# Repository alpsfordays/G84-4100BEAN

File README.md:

# G84-4100BEAN
A ZMK drop-in replacement PCB for the G84-4100 based on the nice!nano and its clones.

## Licence
This project is licenced under the No Wastemans licence. Effectively CC BY-SA 4.0 with exceptions for wastemans, who are afforded no reuse, distribution or manufacture rights whatsoever. For everyone else, it would be great (but not required) if you let me know what you do with it!

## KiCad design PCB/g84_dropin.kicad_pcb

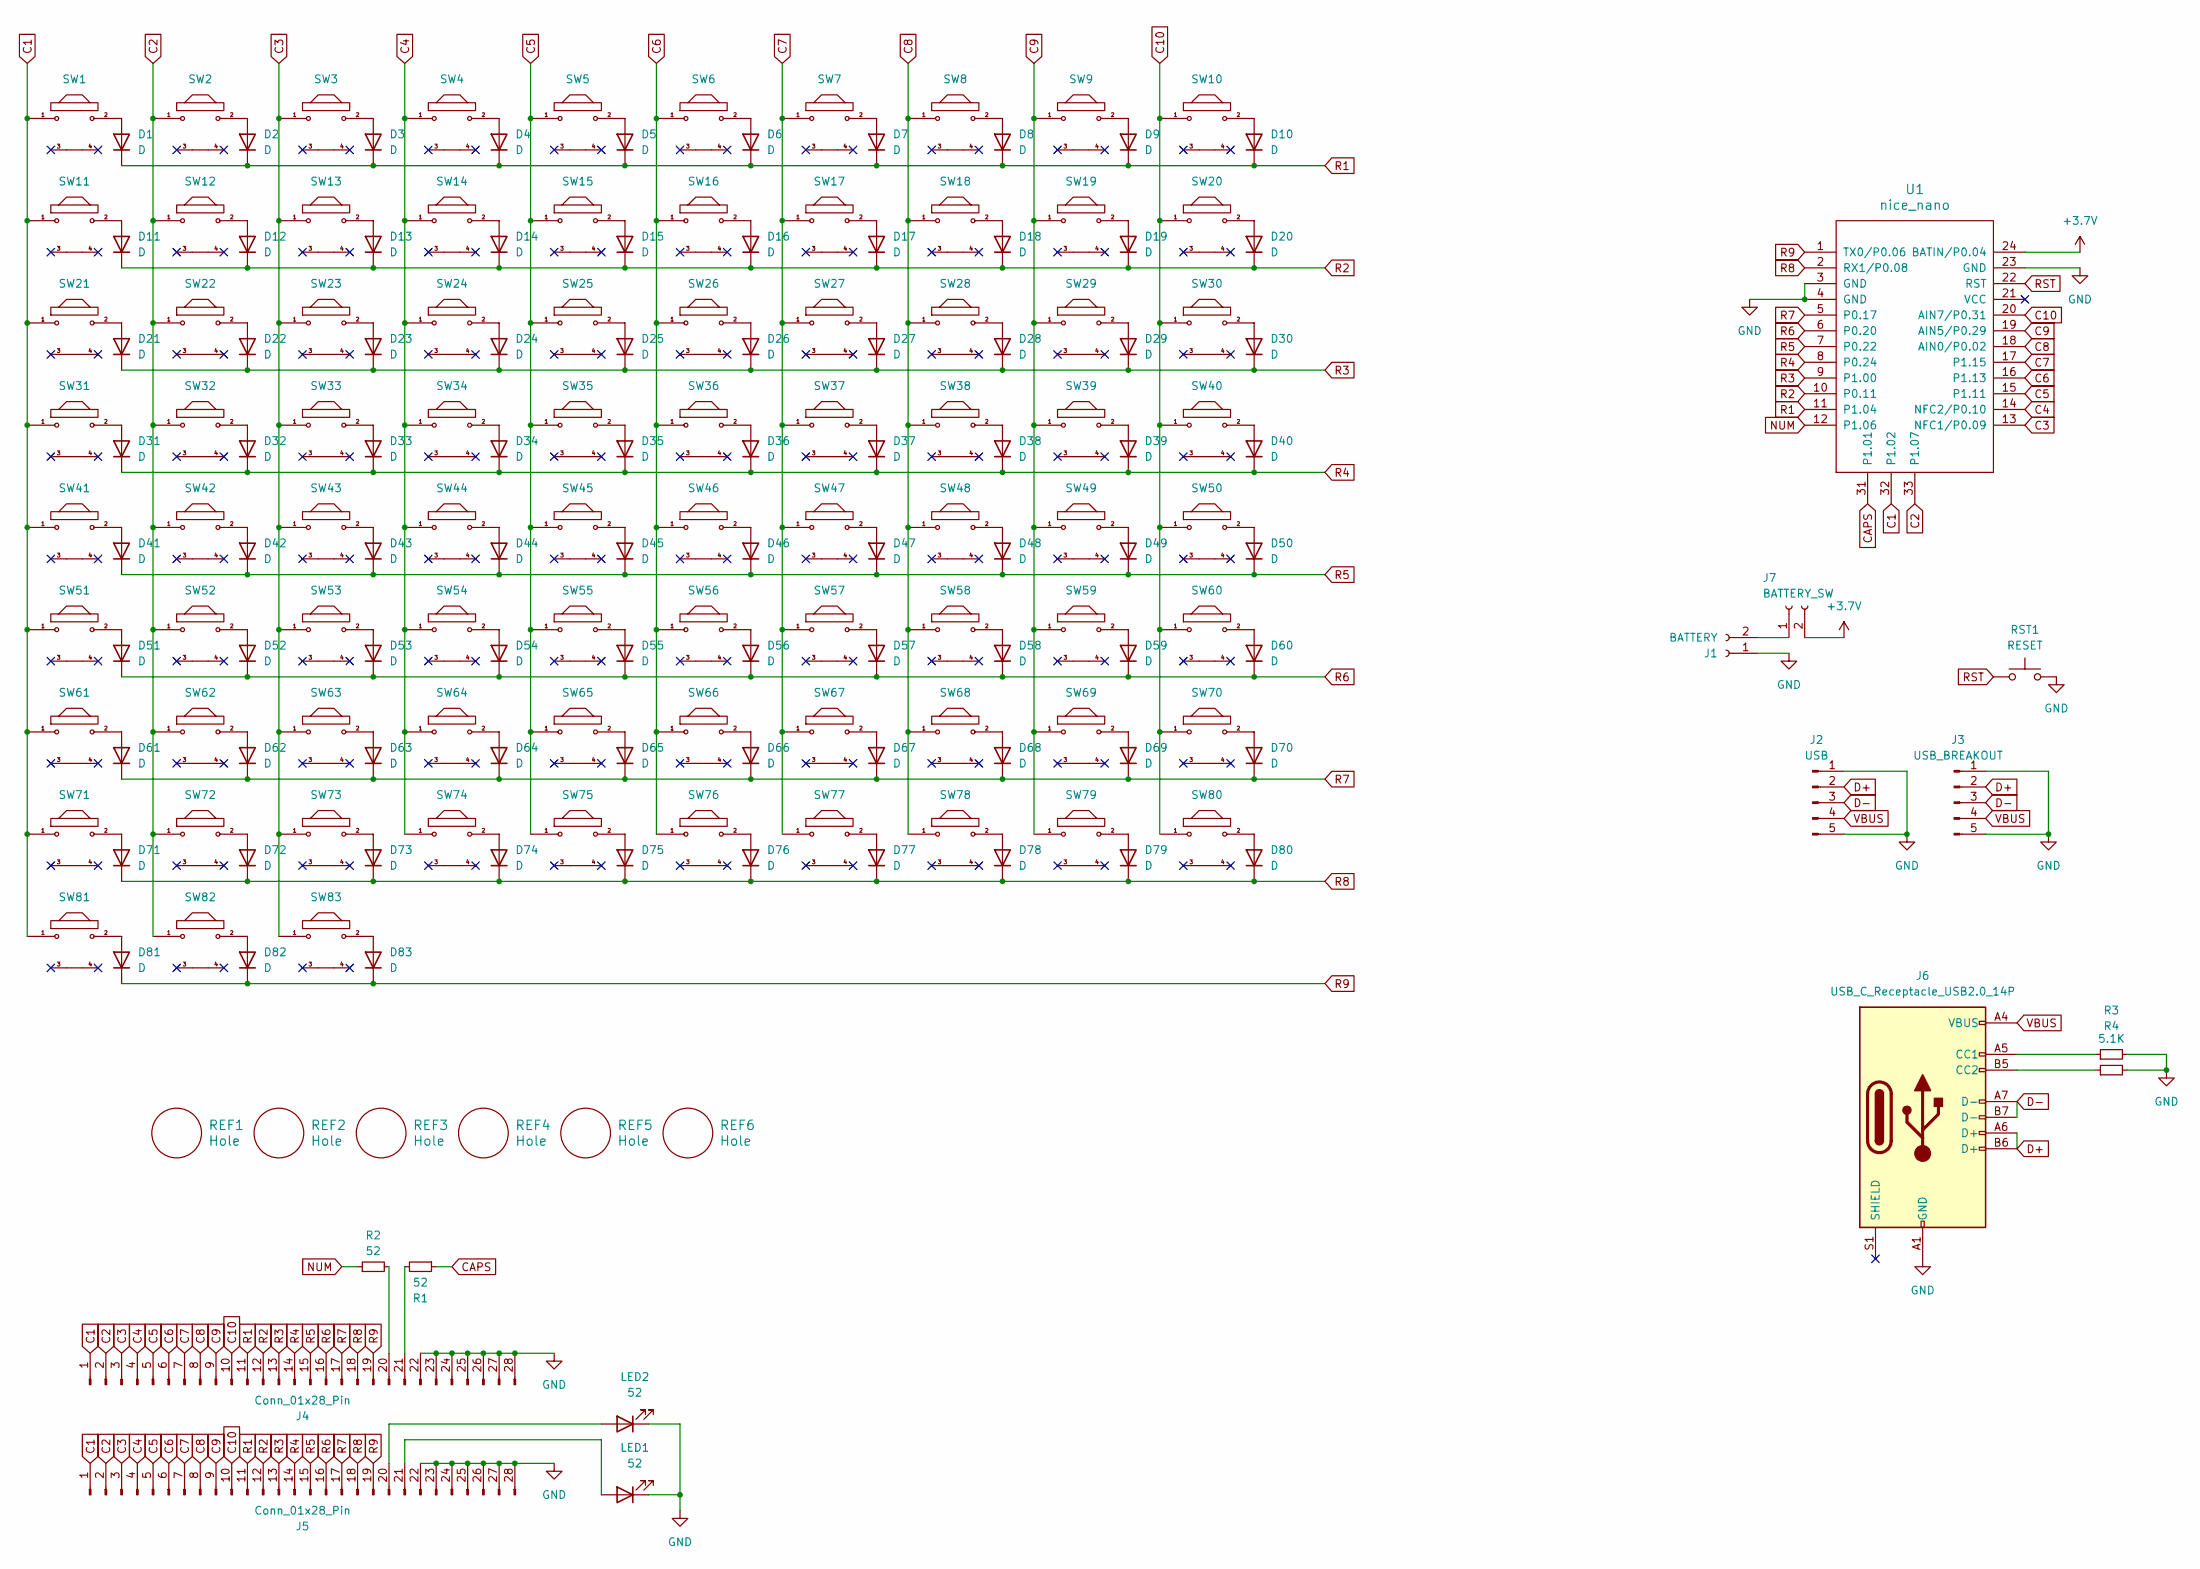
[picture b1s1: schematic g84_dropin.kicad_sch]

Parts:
D1, D2, D3, D4, D5, D6, D7, D8, D9, D10, D11, D12, D13, D14, D15, D16, D17, D18, D19, D20, D21, D22, D23, D24, D25, D26, D27, D28, D29, D30, D31, D32, D33, D34, D35, D36, D37, D38, D39, D40, D41, D42, D43, D44, D45, D46, D47, D48, D49, D50, D51, D52, D53, D54, D55, D56, D57, D58, D59, D60, D61, D62, D63, D64, D65, D66, D67, D68, D69, D70, D71, D72, D73, D74, D75, D76, D77, D78, D79, D80, D81, D82, D83: D; D_0805
J1: BATTERY; PinSocket_1x02_P2.54mm_Vertical
J2: USB; PinHeader_1x05_P1.27mm_Vertical
J3: USB_BREAKOUT; PinHeader_1x05_P2.54mm_Vertical
J4, J5: Conn_01x28_Pin; PinSocket_1x28_P1.27mm_Vertical
J6: USB_C_Receptacle_USB2.0_14P; TYPE-C-31-M-12
J7: BATTERY_SW; PinSocket_1x02_P2.54mm_Vertical
LED1, LED2: 52; D_0805
R1, R2: 52; R_0805
R3, R4: 5.1K; R_0805
REF1, REF2, REF3, REF4, REF5, REF6: Hole; breakaway-mousebites
RST1: RESET; SW_Push_1P1T_XKB_TS-1187A
SW1, SW2, SW3, SW4, SW5, SW6, SW7, SW8, SW9, SW10, SW12, SW13, SW14, SW15, SW16, SW17, SW18, SW19, SW20, SW21, SW22, SW23, SW24, SW25, SW26, SW27, SW28, SW29, SW30, SW32, SW33, SW34, SW35, SW36, SW37, SW38, SW39, SW40, SW42, SW43, SW44, SW45, SW46, SW47, SW48, SW49, SW50, SW51, SW52, SW53, SW54, SW56, SW57, SW58, SW61, SW62, SW68, SW69, SW70, SW71, SW77, SW78: ML; THIN_ML_1u
SW11: ML; THIN_ML_1uL
SW31, SW67, SW80: ML; THIN_ML_1.25u
SW41: ML; THIN_ML_1.75u
SW55: ML; THIN_ML_5u
SW59, SW60, SW63, SW64, SW65, SW66, SW72, SW73, SW74, SW75, SW79, SW81, SW82, SW83: ML; THIN_ML_1uS
SW76: ML; THIN_ML_1.5u
U1: nice_nano; nice_nano_clone_combo

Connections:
+3.7V: J7.2, U1.24 (BATIN/P0.04)
C1: J4.1, J5.1, SW1.1, SW11.1, SW21.1, SW31.1, SW41.1, SW51.1, SW61.1, SW71.1, SW81.1, U1.32 (P1.02)
C2: J4.2, J5.2, SW2.1, SW12.1, SW22.1, SW32.1, SW42.1, SW52.1, SW62.1, SW72.1, SW82.1, U1.33 (P1.07)
C3: J4.3, J5.3, SW3.1, SW13.1, SW23.1, SW33.1, SW43.1, SW53.1, SW63.1, SW73.1, SW83.1, U1.13 (NFC1/P0.09)
C4: J4.4, J5.4, SW4.1, SW14.1, SW24.1, SW34.1, SW44.1, SW54.1, SW64.1, SW74.1, U1.14 (NFC2/P0.10)
C5: J4.5, J5.5, SW5.1, SW15.1, SW25.1, SW35.1, SW45.1, SW55.1, SW65.1, SW75.1, U1.15 (P1.11)
C6: J4.6, J5.6, SW6.1, SW16.1, SW26.1, SW36.1, SW46.1, SW56.1, SW66.1, SW76.1, U1.16 (P1.13)
C7: J4.7, J5.7, SW7.1, SW17.1, SW27.1, SW37.1, SW47.1, SW57.1, SW67.1, SW77.1, U1.17 (P1.15)
C8: J4.8, J5.8, SW8.1, SW18.1, SW28.1, SW38.1, SW48.1, SW58.1, SW68.1, SW78.1, U1.18 (AIN0/P0.02)
C9: J4.9, J5.9, SW9.1, SW19.1, SW29.1, SW39.1, SW49.1, SW59.1, SW69.1, SW79.1, U1.19 (AIN5/P0.29)
C10: J4.10, J5.10, SW10.1, SW20.1, SW30.1, SW40.1, SW50.1, SW60.1, SW70.1, SW80.1, U1.20 (AIN7/P0.31)
CAPS: R1.1, U1.31 (P1.01)
D+: J2.2, J3.2, J6.A6 (D+), J6.B6 (D+)
D-: J2.3, J3.3, J6.A7 (D-), J6.B7 (D-)
GND: J1.1, J2.1, J2.5, J3.1, J3.5, J4.22, J4.23, J4.24, J4.25, J4.26, J4.27, J4.28, J5.22, J5.23, J5.24, J5.25, J5.26, J5.27, J5.28, J6.A1 (GND), J6.A12 (GND), J6.B1 (GND), J6.B12 (GND), LED1.1 (K), LED2.1 (K), R3.2, R4.2, RST1.2, U1.3 (GND), U1.4 (GND), U1.23 (GND)
NUM: R2.1, U1.12 (P1.06)
unnamed: D1.2 (A), SW1.2
unnamed: D2.2 (A), SW2.2
unnamed: D3.2 (A), SW3.2
unnamed: D4.2 (A), SW4.2
unnamed: D5.2 (A), SW5.2
unnamed: D6.2 (A), SW6.2
unnamed: D7.2 (A), SW7.2
unnamed: D8.2 (A), SW8.2
unnamed: D9.2 (A), SW9.2
unnamed: D10.2 (A), SW10.2
unnamed: D11.2 (A), SW11.2
unnamed: D12.2 (A), SW12.2
unnamed: D13.2 (A), SW13.2
unnamed: D14.2 (A), SW14.2
unnamed: D15.2 (A), SW15.2
unnamed: D16.2 (A), SW16.2
unnamed: D17.2 (A), SW17.2
unnamed: D18.2 (A), SW18.2
unnamed: D19.2 (A), SW19.2
unnamed: D20.2 (A), SW20.2
unnamed: D21.2 (A), SW21.2
unnamed: D22.2 (A), SW22.2
unnamed: D23.2 (A), SW23.2
unnamed: D24.2 (A), SW24.2
unnamed: D25.2 (A), SW25.2
unnamed: D26.2 (A), SW26.2
unnamed: D27.2 (A), SW27.2
unnamed: D28.2 (A), SW28.2
unnamed: D29.2 (A), SW29.2
unnamed: D30.2 (A), SW30.2
unnamed: D31.2 (A), SW31.2
unnamed: D32.2 (A), SW32.2
unnamed: D33.2 (A), SW33.2
unnamed: D34.2 (A), SW34.2
unnamed: D35.2 (A), SW35.2
unnamed: D36.2 (A), SW36.2
unnamed: D37.2 (A), SW37.2
unnamed: D38.2 (A), SW38.2
unnamed: D39.2 (A), SW39.2
unnamed: D40.2 (A), SW40.2
unnamed: D41.2 (A), SW41.2
unnamed: D42.2 (A), SW42.2
unnamed: D43.2 (A), SW43.2
unnamed: D44.2 (A), SW44.2
unnamed: D45.2 (A), SW45.2
unnamed: D46.2 (A), SW46.2
unnamed: D47.2 (A), SW47.2
unnamed: D48.2 (A), SW48.2
unnamed: D49.2 (A), SW49.2
unnamed: D50.2 (A), SW50.2
unnamed: D51.2 (A), SW51.2
unnamed: D52.2 (A), SW52.2
unnamed: D53.2 (A), SW53.2
unnamed: D54.2 (A), SW54.2
unnamed: D55.2 (A), SW55.2
unnamed: D56.2 (A), SW56.2
unnamed: D57.2 (A), SW57.2
unnamed: D58.2 (A), SW58.2
unnamed: D59.2 (A), SW59.2
unnamed: D60.2 (A), SW60.2
unnamed: D61.2 (A), SW61.2
unnamed: D62.2 (A), SW62.2
unnamed: D63.2 (A), SW63.2
unnamed: D64.2 (A), SW64.2
unnamed: D65.2 (A), SW65.2
unnamed: D66.2 (A), SW66.2
unnamed: D67.2 (A), SW67.2
unnamed: D68.2 (A), SW68.2
unnamed: D69.2 (A), SW69.2
unnamed: D70.2 (A), SW70.2
unnamed: D71.2 (A), SW71.2
unnamed: D72.2 (A), SW72.2
unnamed: D73.2 (A), SW73.2
unnamed: D74.2 (A), SW74.2
unnamed: D75.2 (A), SW75.2
unnamed: D76.2 (A), SW76.2
unnamed: D77.2 (A), SW77.2
unnamed: D78.2 (A), SW78.2
unnamed: D79.2 (A), SW79.2
unnamed: D80.2 (A), SW80.2
unnamed: D81.2 (A), SW81.2
unnamed: D82.2 (A), SW82.2
unnamed: D83.2 (A), SW83.2
unnamed: J1.2, J7.1
unnamed: J4.20, R2.2
unnamed: J4.21, R1.2
unnamed: J5.20, LED2.2 (A)
unnamed: J5.21, LED1.2 (A)
unnamed: J6.A5 (CC1), R3.1
unnamed: J6.B5 (CC2), R4.1
R1: D1.1 (K), D2.1 (K), D3.1 (K), D4.1 (K), D5.1 (K), D6.1 (K), D7.1 (K), D8.1 (K), D9.1 (K), D10.1 (K), J4.11, J5.11, U1.11 (P1.04)
R2: D11.1 (K), D12.1 (K), D13.1 (K), D14.1 (K), D15.1 (K), D16.1 (K), D17.1 (K), D18.1 (K), D19.1 (K), D20.1 (K), J4.12, J5.12, U1.10 (P0.11)
R3: D21.1 (K), D22.1 (K), D23.1 (K), D24.1 (K), D25.1 (K), D26.1 (K), D27.1 (K), D28.1 (K), D29.1 (K), D30.1 (K), J4.13, J5.13, U1.9 (P1.00)
R4: D31.1 (K), D32.1 (K), D33.1 (K), D34.1 (K), D35.1 (K), D36.1 (K), D37.1 (K), D38.1 (K), D39.1 (K), D40.1 (K), J4.14, J5.14, U1.8 (P0.24)
R5: D41.1 (K), D42.1 (K), D43.1 (K), D44.1 (K), D45.1 (K), D46.1 (K), D47.1 (K), D48.1 (K), D49.1 (K), D50.1 (K), J4.15, J5.15, U1.7 (P0.22)
R6: D51.1 (K), D52.1 (K), D53.1 (K), D54.1 (K), D55.1 (K), D56.1 (K), D57.1 (K), D58.1 (K), D59.1 (K), D60.1 (K), J4.16, J5.16, U1.6 (P0.20)
R7: D61.1 (K), D62.1 (K), D63.1 (K), D64.1 (K), D65.1 (K), D66.1 (K), D67.1 (K), D68.1 (K), D69.1 (K), D70.1 (K), J4.17, J5.17, U1.5 (P0.17)
R8: D71.1 (K), D72.1 (K), D73.1 (K), D74.1 (K), D75.1 (K), D76.1 (K), D77.1 (K), D78.1 (K), D79.1 (K), D80.1 (K), J4.18, J5.18, U1.2 (RX1/P0.08)
R9: D81.1 (K), D82.1 (K), D83.1 (K), J4.19, J5.19, U1.1 (TX0/P0.06)
RST: RST1.1, U1.22 (RST)
VBUS: J2.4, J3.4, J6.A4 (VBUS), J6.A9 (VBUS), J6.B4 (VBUS), J6.B9 (VBUS)

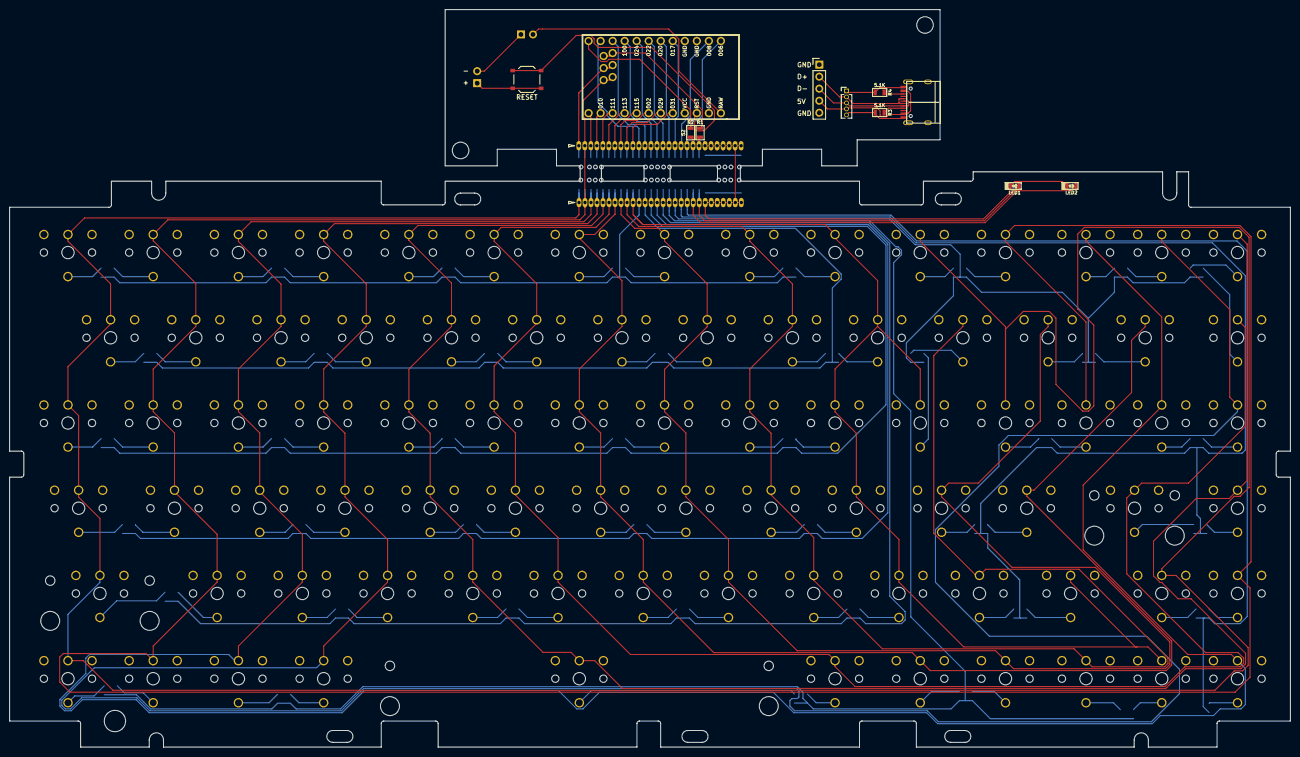
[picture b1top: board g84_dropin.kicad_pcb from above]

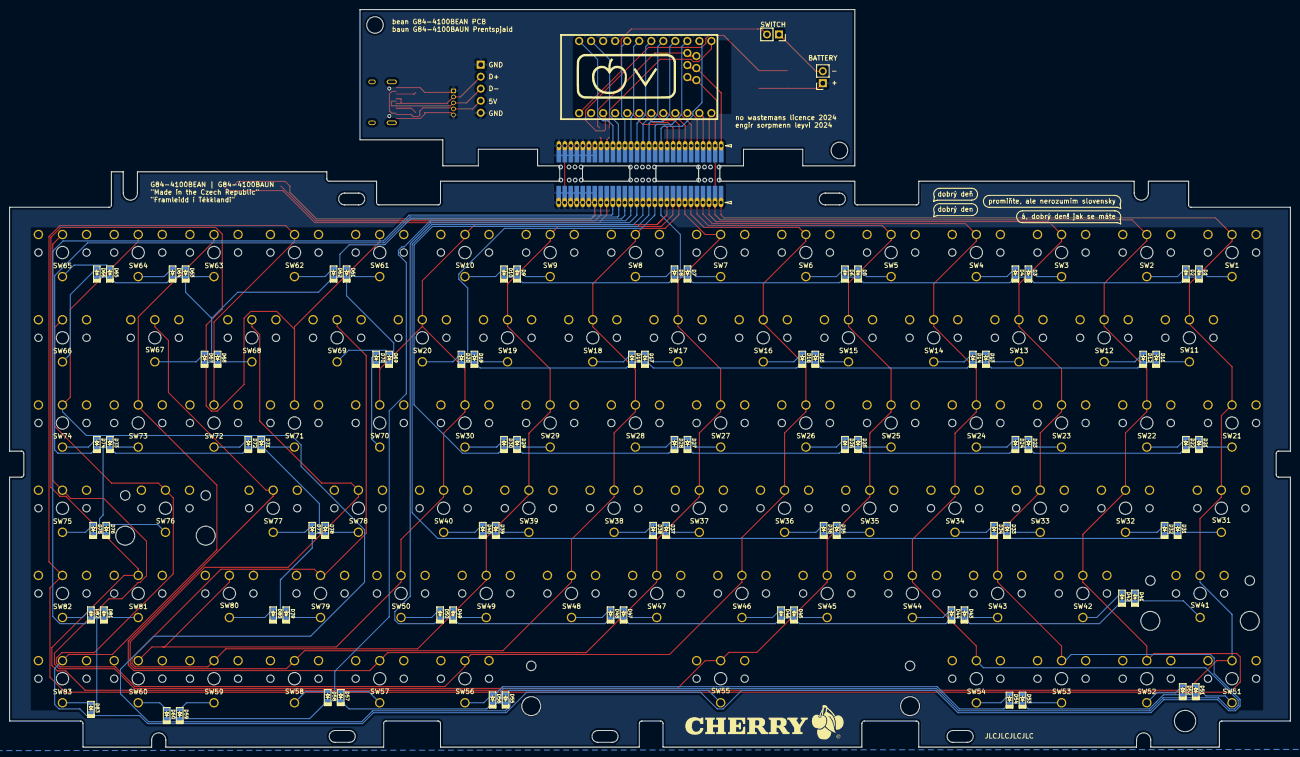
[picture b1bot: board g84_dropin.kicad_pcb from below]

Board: 2 copper layers, 270.5 x 155.8 mm, 189 parts (87 on the bottom side), 117 nets.

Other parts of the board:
G1, G4: LOGO

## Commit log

2024-05-19 Added initial files and readme.md
2024-05-19 Added gerbers
2024-05-19 Edit readme
